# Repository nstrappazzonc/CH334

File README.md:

# CH334

Este es un simple IC para construir un HUB USB 2.0 de muy bajo coste, diseñado y fabricado en china por [Jiangsu Heng Qin Ltd. (WCH)](http://www.wch-ic.com). De momento nos vamos a centrar en el CH334U que tiene unas prestaciones muy versátiles, entre ellas destacan las siguientes:

- HUB USB 2.0 de 4 puertos de velocidad máxima de 480Mbps.
- Compatible con USB 1.1
- Posibilidad de configurar el VID y PID mediante un EEPROM externo.
- Adicionalmente tiene detección de GANG, soporta el modo MTT.
- Soporta ESD de hasta 6KV (Clase 3A)

En la imagen no mostramos el resto de los puertos USB para evitar de complicar la imagen evitando la simple percepción del circuito mínimo.

Puedes conseguir los IC en la tienda oficial de [AliExpress](https://wchofficialstore.es.aliexpress.com/store/1100367542) o en [LCSC](https://www.lcsc.com).

## Componentes

Use los siguientes componentes para construir el circuito mínimo:

- Un IC CH334U.
- Oscilador de cristal de 12Mhz de 12-20pF 20ppm.
- Condensador de 0.1uF (Código: 104, Cantidad: 2).
- Condensador de 1uF (Código: 105, Cantidad: 1).
- Condensador de 10uF (Código: 106, Cantidad: 1).
- Diodo 1N4001.

## Esquema minimo del circuito

## Consejos

Haga uso de las siguientes consideraciones para construir y verificar el circuito mínimo con el fin de descartar cualquier problema. Algunos comentarios son de mi propia experiencia y otros son obtenidos del [foro oficial](https://www.wch.cn/bbs/search?q=CH334&page=1) que está en chino.

- Asegúrese de tener un cable USB que funcione, no solo el VCC y el GND, sino también D+ y D-.
- Para el CH334U, mida con un voltímetro los siguientes pines: 13, 17, 21, 26. Los cuatro deben tener alrededor de 3.3v.
- El oscilador de cristal de 12Mhz con las siguientes características: entre 12pF y 20pF y 20ppm.

## Proyectos relacionados

- [CH340 - USB 2.0 to Serial](https://github.com/nstrappazzonc/CH340)
- [CH552 - 8-bits MCU - 8051](https://github.com/nstrappazzonc/CH552)
- [CH9141 - Bluetooth Serial Transparent](https://github.com/nstrappazzonc/CH9141)

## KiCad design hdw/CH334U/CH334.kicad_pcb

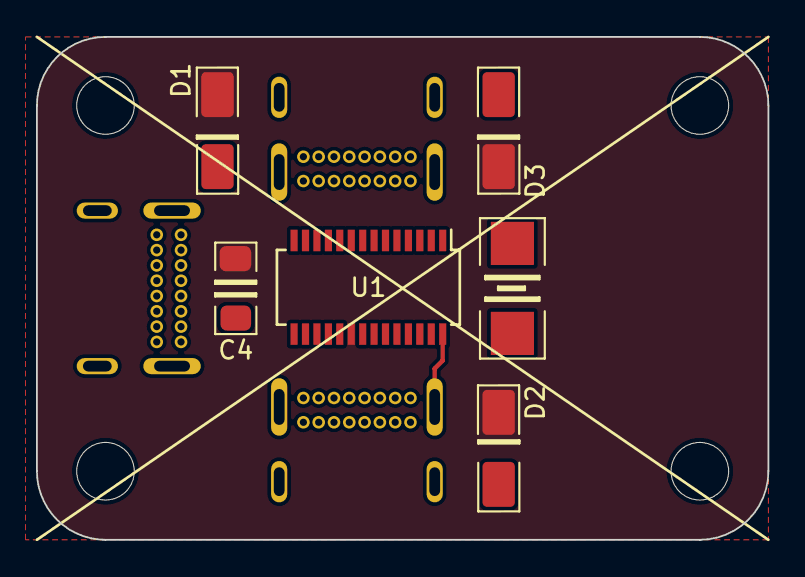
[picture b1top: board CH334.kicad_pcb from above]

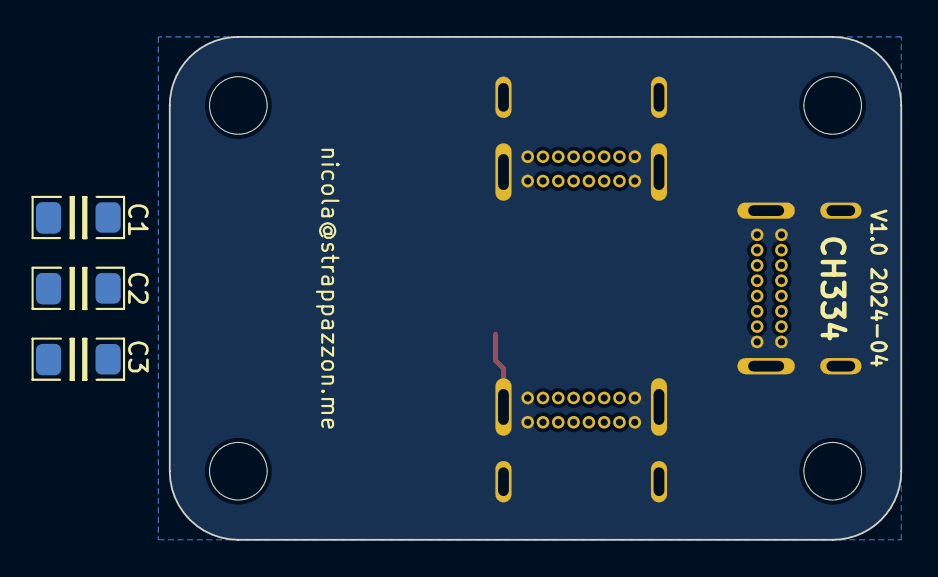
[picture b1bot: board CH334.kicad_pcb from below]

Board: 2 copper layers, 40.6 x 27.9 mm, 16 parts (3 on the bottom side), 14 nets.

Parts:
C1: 10uF; C1206
C2: 0.1uF; C1206
C3, C4: 1uF; C1206
D1, D3: 1N4001; SMA_DO_214AC
D2: 1N4001; D_SMA
H1, H2, H3, H4: MountingHole; MountingHole_3.2mm_M3
P1, P2, P3: USB_C_Receptacle_USB2.0; TH_USB_C
U1: CH334U; SSOP-28_3.9x9.9mm_P0.635mm
Y1: 12MHz; SMD_O5032

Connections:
DM1: P2.A7 (D-), P2.B7 (D-), U1.10 (DM1)
DM2: P3.A7 (D-), P3.B7 (D-), U1.8 (DM2)
DMU: P1.A7 (D-), P1.B7 (D-), U1.15 (DMU)
DP1: P2.A6 (D+), P2.B6 (D+), U1.11 (DP1)
DP2: P3.A6 (D+), P3.B6 (D+), U1.9 (DP2)
DPU: P1.A6 (D+), P1.B6 (D+), U1.16 (DPU)
GND: C1.2, C2.2, C3.2, C4.1, P1.A1 (GND), P1.A12 (GND), P1.B1 (GND), P1.B12 (GND), P1.S1 (SHIELD), P2.A1 (GND), P2.A12 (GND), P2.B1 (GND), P2.B12 (GND), P2.S1 (SHIELD), P3.A1 (GND), P3.A12 (GND), P3.B1 (GND), P3.B12 (GND), P3.S1 (SHIELD), U1.1 (GND), U1.12 (GND), U1.28 (GND)
unnamed: C1.1, C2.1, C3.1, U1.13 (VDD33), U1.21 (VDD33)
unnamed: D1.2 (A), P1.A4 (VBUS), P1.A9 (VBUS), P1.B4 (VBUS), P1.B9 (VBUS)
unnamed: D2.1 (K), P2.A4 (VBUS), P2.A9 (VBUS), P2.B4 (VBUS), P2.B9 (VBUS)
unnamed: D3.1 (K), P3.A4 (VBUS), P3.A9 (VBUS), P3.B4 (VBUS), P3.B9 (VBUS)
unnamed: U1.3 (XI), Y1.1
unnamed: U1.2 (XO), Y1.2
VCC: C4.2, D1.1 (K), D2.2 (A), D3.2 (A), U1.20 (V5)

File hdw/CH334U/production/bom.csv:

Designator,Footprint,Quantity,Value,LCSC Part #
C1,C1206,1,10uF,
C2,C1206,1,0.1uF,
"C3, C4",C1206,2,1uF,
"D1, D3",SMA_DO_214AC,2,1N4001,
D2,D_SMA,1,1N4001,
"H1, H2, H3, H4",MountingHole_3.2mm_M3,4,MountingHole,
"P1, P2, P3",TH_USB_C,3,USB_C_Receptacle_USB2.0,
U1,SSOP-28_3.9x9.9mm_P0.635mm,1,CH334U,
Y1,SMD_O5032,1,12MHz,

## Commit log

2024-01-06 doc - update
2024-01-07 doc - update links
2024-06-10 update schematic
